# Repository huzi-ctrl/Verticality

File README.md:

# CanSat — Team Verticality (RP2040 Avionics & Dinoflagellate Bioluminescence Payload)

**Team Verticality** (Lancaster University School of Mathematics — UK CanSat Competition) is a 4-layer **52.0 mm round** avionics and dual-chamber biological payload controller built from scratch around the **Raspberry Pi RP2040** microcontroller.

Our secondary mission investigates **stress-induced mechano-bioluminescence** in marine dinoflagellates (***Pyrocystis fusiformis*** primary species; ***Pyrocystis lunula*** from Darwin Biological UK as the verified UK-stocked backup species) during rocket boost, parachute deployment, descent, and landing impact:
- **Chamber A (Warmed Experimental Culture)**: Actively maintained at **$22.0 \pm 1.0\text{ }^\circ\text{C}$** via a closed-loop PID controller driving an off-board $15\text{ }\Omega$, $2\text{ W}$ axial heating resistor (`R8`, switched by `Q1` `AO3400A` MOSFET at $1\text{ kHz}$ PWM) with a $10\text{ k}\Omega$ thin-film NTC thermistor (`TH1`). Safety cut-outs disable the heater if battery voltage drops below $3.50\text{ V}$ or Chamber A temperature reaches $30.0\text{ }^\circ\text{C}$.
- **Chamber B (Unheated Ambient Control)**: Identical optical geometry and cell concentration, left unheated with a matched $10\text{ k}\Omega$ NTC thermistor (`TH2`) to isolate temperature effects from mechanical shear and jerk ($\text{d}a/\text{d}t$).
- **Dual High-Sensitivity Optical Readout**: Two **AMS TSL2591** digital light sensor breakouts (`U7` on `I2C0`, `U8` on `I2C1` — separate hardware $\text{I}^2\text{C}$ buses because the `TSL2591` has a fixed `0x29` address) operating at $9876\times$ gain ($200\text{ ms}$ integration) inside light-tight black PETG chambers.
- **Pre-Touchdown Landing Leg Deployment & Upright Recovery**: Three 3D-printed curved landing legs folded against the **$64\text{ mm} \times 110\text{ mm}$** three-tier PETG cylindrical shell are released **during `DESCENT` before touchdown** — at **$150\text{ m}$ above pad altitude or $15\text{ s}$ after apogee, whichever comes first** — via an `MG90S` semi-metal servo (`J6`, low-side power-gated by `Q2` `AO3400A` so idle servo current is $0\text{ mA}$). The legs swing out to a **$140\text{ mm}$ triangular stance** while a $\sim 62\text{ g}$ steel ballast hatch lowers the centre of gravity to $z = 34\text{ mm}$ ($27\text{ mm}$ below the $61\text{ mm}$ leg pivot plane, giving a $>44^\circ$ static tip-over angle) so the top-mounted $433\text{ MHz}$ helical antenna stays upright after landing.

---

## 1. 3D PCB Renders & Layout Gallery

| Isometric 3D Render (`CanSat.kicad_pcb`) | Top View (`F.Cu` — RP2040, Flash, LDO, Ra-02, Power Stage) | Bottom View (`B.Cu` — Solid Ground Return & Signal Fanout) |
| :---: | :---: | :---: |
|  |  |  |

---

## 2. Mechanical Architecture, Landing Legs & Power Budget

### Three-Tier $64\text{ mm} \times 110\text{ mm}$ Shell & $52.0\text{ mm}$ Round PCB
The satellite body is a **$64\text{ mm}$ outer diameter $\times 110\text{ mm}$ tall** three-tier 3D-printed PETG structure clamped by **three $115\text{ mm}$ M3 A2 stainless steel threaded tie-rods** (`H1`, `H2`, `H3` on a $22.5\text{ mm}$ bolt-circle radius at $90^\circ, 210^\circ, 330^\circ$) to a top bulkhead lifting eyebolt:
1. **Top Tier ($40\text{ mm}$ height)**: Houses the **52.0 mm round 4-layer PCB**, the `Ai-Thinker Ra-02` ($433.175\text{ MHz}$ LoRa transceiver), U.FL pigtail, $21\text{ mm}$ helical antenna (`BW433SNX21-5W2`), `GY-BMP280-3.3` barometer (`U6`), and `Adafruit ADXL375` $\pm 200\text{ g}$ accelerometer (`U4`).
2. **Middle Tier ($42\text{ mm}$ height)**: Contains the light-tight black PETG **Chamber A** (heated to $22 \pm 1\text{ }^\circ\text{C}$ via `R8` $15\text{ }\Omega$ $2\text{ W}$ axial resistor and `TH1` NTC) and **Chamber B** (unheated control with `TH2` NTC), each with a sealed dinoflagellate vial and dedicated `TSL2591` optical sensor (`U7`, `U8`).
3. **Bottom Tier ($28\text{ mm}$ height)**: Houses the **flat `103450` $3.7\text{ V}$, $2000\text{ mAh}$ protected LiPo pouch cell** ($50 \times 34 \times 10\text{ mm}$ — selected specifically because a cylindrical 18650 cell is $65\text{ mm}$ long and cannot fit inside the $28\text{ mm}$ bottom tier or $64\text{ mm}$ diameter), the `MG90S` leg-release servo (`J6`), and the $\sim 62\text{ g}$ steel ballast hatch.

### Pre-Touchdown Leg Release Mechanism
- **Stowed Configuration**: Three curved 3D-printed PETG/TPU legs wrap flush against the outer wall during rocket integration and boost, held by a single nylon retention loop on the `MG90S` servo horn (`J6`).
- **In-Air Release (`STATE_DESCENT`)**: The flight software strictly locks out `Q2` (`GP9 = 0`) during `SELF_TEST`, `PAD`, and `BOOST`. Once apogee is passed (`STATE_DESCENT`) and either **relative altitude drops below $150.0\text{ m}$ above the pad OR $15.0\text{ s}$ have elapsed since apogee**, `GP9` turns on `Q2` (`AO3400A`) for $700\text{ ms}$ while `GP10` drives a $50\text{ Hz}$ PWM command to rotate the `MG90S` horn $120^\circ$, releasing all three legs before touchdown.
- **Self-Righting Geometry**: Torsion hinges open the three legs to a **$140\text{ mm}$ footprint** with hinges at $z = 61\text{ mm}$ above the base and the ballasted centre of gravity at $z = 34\text{ mm}$ ($27\text{ mm}$ below the pivot plane), providing a $>44^\circ$ static stability margin on uneven ground.

---

## 3. 4-Layer PCB Stackup, Layout Rules & Audit Compliance

The board ([`CanSat.kicad_pcb`](./CanSat.kicad_pcb)) is a **52.0 mm diameter**, $1.6\text{ mm}$ thick 4-layer FR-4 PCB designed to JLCPCB 4-layer manufacturing rules and verified against [`reports/CanSat_PCB_Design_Guide__Team_Verticality__rev2.pdf`](./reports/CanSat_PCB_Design_Guide__Team_Verticality__rev2.pdf):

| Layer | Copper Name | Plane / Function | Design Notes |
| :--- | :--- | :--- | :--- |
| **Layer 1** | `F.Cu` | Top Component & High-Speed Signal Layer | All **46 SMT components** placed on top side only (single-sided JLCPCB Economic PCBA); $90\text{ }\Omega$ differential USB (`R2`/`R3` = $22\text{ }\Omega$), short QSPI (`U2`), `12MHz` crystal (`Y1` + $33\text{ pF}$ C0G load caps `C10`/`C11`), and `0.6 mm` high-current switched paths (`Net-(Q1-D)` and `Net-(J6-Pin_1)`). |
| **Layer 2** | `In1.Cu` | Unbroken `GND` Reference Plane | Solid continuous ground reference plane beneath all high-speed, RF (`U5`), and analog (`ADC0..ADC2`) traces. |
| **Layer 3** | `In2.Cu` | `+3V3` Power Plane | Solid $+3.3\text{ V}$ distribution plane fed by `U3` (`MCP1700-3302E/TO`), with an explicit keepout cutout (`XTAL_KEEPOUT`) beneath `Y1`, `C10`, `C11`, and `R1` so crystal signals reference only `In1.Cu` (`GND`). |
| **Layer 4** | `B.Cu` | Bottom Signal Routing & `GND` Pour | Secondary signal fanout with stitched `GND` copper pour. Zero components on `B.Cu`. |

### Key Hardware & DFM Highlights
- **Strict SMT vs. Hand-Fit / Wire-Pad Separation**:
  - **46 SMT parts** (14 unique LCSC lines: 13 Basic + 1 Extended `RP2040` `C2040`, 157 SMT joints/board) have `LCSC` part numbers populated and are exported to [`production/parts_jlcpcb.csv`](./production/parts_jlcpcb.csv) and [`production/positions_jlcpcb.csv`](./production/positions_jlcpcb.csv).
  - **All 29 non-SMT items** — hand-fitted through-hole/castellated parts (`U3`, `U5`, `C22`, `J1`, `SW1`, `R8`), DNP $\text{I}^2\text{C}$ pull-up footprints (`R18–R21`), off-board module wire-pad groups (`U4`, `U6`, `U7`, `U8`, `TH1`, `TH2`, `J2`, `J3`, `J4`, `J5`, `J6`), test points (`TP1–TP5`), and mounting holes (`H1–H3`) — have **both `Exclude from bom` and `Exclude from Position Files`** set in [`CanSat.kicad_sch`](./CanSat.kicad_sch) and [`CanSat.kicad_pcb`](./CanSat.kicad_pcb).
- **High-Current MOSFET Via Arrays & Trace Widths**:
  - `Q1` (Heater `AO3400A`) and `Q2` (Servo `AO3400A`) each have **three `0.6 mm / 0.3 mm` `GND` vias** at their source pads (`Q1.2` and `Q2.2`) to handle the $\sim 1\text{ A}$ servo stall current and $250\text{ mA}$ heater current with minimal ground bounce.
  - `HighCurrent` netclass contains only the switched drain paths `Net-(Q1-D)` and `Net-(J6-Pin_1)` routed at **`0.6 mm` width**, while the logic gate nets (`/HEATER`, `/SERVO_P`, `/SERVO_S`) use signal widths.
- **Via Sizing & Standard JLCPCB $2.00 Base Tier Optimization**:
  - Every via on the board uses a **`0.30 mm` drill minimum** across all 112 vias (90 at `0.45 / 0.30 mm`, 3 at `0.50 / 0.30 mm`, and 19 at `0.60 / 0.30 mm` — zero `< 0.30 mm` vias remain), with `min_through_hole_diameter: 0.30` and `min_via_annular_width: 0.075` mm configured in [`CanSat.kicad_pro`](./CanSat.kicad_pro). This qualifies the design for JLCPCB's standard **`0.3mm / (0.4/0.45mm)`** pricing tier ($2.00 base price) instead of triggering advanced high-precision surcharges.
  - All 12 wire-pad groups (`J1/SW1`, `J2 BOOTSEL` using `CanSat_Modules:Pad_2pad_GND_SIG`, `J3 SWD`, `J4 USB`, `J5 RUN`, `J6 Servo`, `R8 Heater`, `TH1`, `TH2`, `U4`, `U6`, `U7`, `U8`) are protected by `WIRE_PADS` keepout zones prohibiting vias under solder pads, and teardrops are enabled on all pads and vias.
- **DRC & ERC Verification Status**:
  * [`DRC.rpt`](./DRC.rpt): **0 unconnected pads, 0 footprint errors, 0 schematic parity errors**.
  * **16 DFM Clearances Documented**:
    * **4 Hole-to-Hole Spacing Notices**: In the tight $0.4\text{ mm}$ pitch RP2040 escape fanout, adjacent $0.3\text{ mm}$ drill vias sit at $0.407\text{ mm}$ (`/INT_A` vs `/INT_B`) to $0.450\text{ mm}$ drill-edge spacing. While flagged against KiCad's generic $0.500\text{ mm}$ default rule, these safely clear JLCPCB's 4-layer CAM drill-to-drill capability of $\ge 0.25\text{ mm}$ (and $\ge 0.254\text{ mm}$ same-net).
    * **12 Drill-to-Track Clearances**: With $0.45\text{ mm}$ pads, $0.30\text{ mm}$ drills ($0.075\text{ mm}$ annular ring), and standard $0.15\text{ mm}$ trace clearance, physical drill-to-trace distance is $0.205\text{ mm} - 0.235\text{ mm}$, fully compliant with JLCPCB's 4-layer hole-to-track minimum of $\ge 0.20\text{ mm}$.
  * [`ERC.rpt`](./ERC.rpt): **0 ERC errors** (50 warnings for net-label wire stubs and unspecified pins per design guide).

---

## 4. Complete RP2040 Pin Allocation & Wire-Pad Pin Orders

### RP2040 (`U1`) GPIO & Peripheral Map

| RP2040 Pin | GPIO / Function | Schematic Net | Connected Component & Function |
| :---: | :--- | :--- | :--- |
| **Pin 2** | `GP0` (`UART0_TX`) | `/RX` | `TP4` UART Debug Header (MCU Transmit -> Adapter RX) |
| **Pin 3** | `GP1` (`UART0_RX`) | `/TX` | `TP5` UART Debug Header (MCU Receive <- Adapter TX) |
| **Pin 4** | `GP2` ( IRQ ) | `/INT_A` | `U7` (`TSL2591` Chamber A) Interrupt Output |
| **Pin 5** | `GP3` ( IRQ ) | `/INT_B` | `U8` (`TSL2591` Chamber B) Interrupt Output |
| **Pin 6** | `GP4` (`I2C0_SDA`) | `/SDA0` | `U7` (`TSL2591` Chamber A) $\text{I}^2\text{C}$ Data (`R18` DNP; pull-up on module) |
| **Pin 7** | `GP5` (`I2C0_SCL`) | `/SCL0` | `U7` (`TSL2591` Chamber A) $\text{I}^2\text{C}$ Clock (`R19` DNP; pull-up on module) |
| **Pin 8** | `GP6` (`I2C1_SDA`) | `/SDA1` | `U8` (`TSL2591` Chamber B) $\text{I}^2\text{C}$ Data (`R21` DNP; pull-up on module) |
| **Pin 9** | `GP7` (`I2C1_SCL`) | `/SCL1` | `U8` (`TSL2591` Chamber B) $\text{I}^2\text{C}$ Clock (`R20` DNP; pull-up on module) |
| **Pin 11** | `GP8` (`PWM4_A`) | `/HEATER` | `R7` ($100\text{ }\Omega$) & `R9` ($100\text{ k}\Omega$) $\rightarrow$ `Q1` (`AO3400A`) Gate $\rightarrow$ `R8` ($15\text{ }\Omega$ $2\text{ W}$ Chamber A Heater) |
| **Pin 12** | `GP9` (GPIO Out) | `/SERVO_P` | `R10` ($100\text{ }\Omega$) & `R11` ($100\text{ k}\Omega$) $\rightarrow$ `Q2` (`AO3400A`) Gate $\rightarrow$ `J6` (`MG90S` Low-Side Power Switch) |
| **Pin 13** | `GP10` (`PWM5_A`) | `/SERVO_S` | `R17` ($10\text{ k}\Omega$ pull-down) $\rightarrow$ `J6` Pin 3 (`MG90S` $50\text{ Hz}$ Servo PWM Signal) |
| **Pin 14** | `GP11` (`SPI1_CSn`) | `/PRESS_CS` | `U6` (`GY-BMP280-3.3`) SPI Chip Select |
| **Pin 15** | `GP12` (`SPI1_RX`) | `/IMU_MISO` | `U4` (`ADXL375`) & `U6` (`BMP280`) Shared `SPI1` MISO |
| **Pin 16** | `GP13` (`SPI1_CSn`) | `/IMU_CS` | `U4` (`ADXL375` $\pm 200\text{ g}$ Accelerometer) SPI Chip Select |
| **Pin 17** | `GP14` (`SPI1_SCK`) | `/IMU_SCLK` | `U4` (`ADXL375`) & `U6` (`BMP280`) Shared `SPI1` Clock |
| **Pin 18** | `GP15` (`SPI1_TX`) | `/IMU_MOSI` | `U4` (`ADXL375`) & `U6` (`BMP280`) Shared `SPI1` MOSI |
| **Pin 27** | `GP16` (`SPI0_RX`) | `/RA_MISO` | `U5` (`Ai-Thinker Ra-02` `SX1278` $433.175\text{ MHz}$ LoRa) MISO |
| **Pin 28** | `GP17` (`SPI0_CSn`) | `/RA_CS` | `U5` (`Ai-Thinker Ra-02`) NSS / Chip Select |
| **Pin 29** | `GP18` (`SPI0_SCK`) | `/RA_SCLK` | `U5` (`Ai-Thinker Ra-02`) SCK |
| **Pin 30** | `GP19` (`SPI0_TX`) | `/RA_MOSI` | `U5` (`Ai-Thinker Ra-02`) MOSI |
| **Pin 31** | `GP20` (GPIO Out) | `/RA_RESET` | `U5` (`Ai-Thinker Ra-02`) Hardware Reset |
| **Pin 32** | `GP21` (GPIO In) | `/RA_DIO0` | `U5` (`Ai-Thinker Ra-02`) `DIO0` TxDone / RxDone IRQ |
| **Pin 34** | `GP22` (GPIO In) | `/IMU_INT1` | `U4` (`ADXL375`) `INT1` High-G Shock Interrupt |
| **Pin 37** | `GP25` (GPIO Out) | `/LED` | `R12` ($1\text{ k}\Omega$) $\rightarrow$ `D1` (`KT-0805G` Green Status LED) |
| **Pin 38** | `GP26 / ADC0` | `/BATT_SENSE`| `R15` ($100\text{ k}\Omega$) / `R16` ($100\text{ k}\Omega$) $2:1$ Divider + `C25` ($100\text{ nF}$) from `/VBAT` |
| **Pin 39** | `GP27 / ADC1` | `/NTC_A` | `R13` ($10\text{ k}\Omega$ to `+3V3`) + `C23` ($100\text{ nF}$) + `TH1` (Chamber A $10\text{ k}\Omega$ NTC) |
| **Pin 40** | `GP28 / ADC2` | `/NTC_B` | `R14` ($10\text{ k}\Omega$ to `+3V3`) + `C24` ($100\text{ nF}$) + `TH2` (Chamber B $10\text{ k}\Omega$ NTC) |
| **Pin 46/47**| `USB_DM / USB_DP` | `/D-`, `/D+` | `R2` ($22\text{ }\Omega$) & `R3` ($22\text{ }\Omega$) $\rightarrow$ `J4` (`USB_3pad_wire`) |
| **Pin 51–56**| `QSPI_SD0..3, SCLK, SS` | `/SD0..3, /SCLK, /SS` | `U2` (`W25Q128JVSIQ` $16\text{ MB}$ QSPI Flash) + `R5` ($10\text{ k}\Omega$) + `R4` ($1\text{ k}\Omega$ to `J2` `BOOTSEL`) |

### Off-Board Wire-Pad Pin Orders (Design Guide Rev 2 Section 6)

| Footprint Ref | Module / Function | Pad Order on PCB |
| :---: | :--- | :--- |
| **`J1`** | Battery Input (`JST B2B-PH-K-S`) | `1 = /VBAT_R` (Battery $+$), `2 = GND` (Check LiPo red/black polarity before plugging in) |
| **`SW1`** | Master Slide Switch (`SS-12D00G3`) | `1 = open`, `2 = /VBAT_R` (middle common pin), `3 = /VBAT` (switched rail) |
| **`J2`** | `BOOTSEL` (`Pad_2pad_GND_SIG`) | `1 = GND`, `2 = Net-(J2-Pin_2)` (to `R4` $1\text{ k}\Omega \rightarrow \text{/SS}$) |
| **`J3`** | `SWD` (`SWD_3pad`) | `1 = /SWDIO`, `2 = GND`, `3 = /SWCLK` |
| **`J4`** | `USB` (`USB_3pad_wire`) | `1 = GND`, `2 = /D-`, `3 = /D+` (Board powered from battery during USB flashing) |
| **`J5`** | `RUN` (`Pad_2pad_GND_SIG`) | `1 = GND`, `2 = /RUN` |
| **`J6`** | `MG90S` Servo (`Pad_3pad_Servo`) | `1 = Net-(J6-Pin_1)` (switched GND via `Q2` — brown), `2 = /VBAT` (red), `3 = /SERVO_S` (orange) |
| **`R8`** | Chamber A Heater ($15\text{ }\Omega$ $2\text{ W}$) | `1 = Net-(Q1-D)` (switched GND via `Q1`), `2 = /VBAT` |
| **`TH1` / `TH2`** | Chamber A / B NTC ($10\text{ k}\Omega$) | `1 = /NTC_A` (or `/NTC_B`), `2 = GND` |
| **`U4`** | `ADXL375` Breakout (`Pad_7pad_ADXL375`) | `1/6 = +3V3`, `2/4/5 = GND`, `7 = /IMU_CS`, `8 = /IMU_INT1`, `12 = /IMU_MISO`, `13 = /IMU_MOSI`, `14 = /IMU_SCLK` |
| **`U6`** | `GY-BMP280-3.3` (`Pad_6pad_BMP280`) | `1/7 = GND`, `2 = /PRESS_CS`, `3 = /IMU_MOSI`, `4 = /IMU_SCLK`, `5 = /IMU_MISO`, `6/8 = +3V3` |
| **`U7` / `U8`** | `TSL2591` Breakout A / B (`TSL2591_module_5pad`) | `1 = +3V3`, `2 = GND`, `3 = /SDA0` (`/SDA1`), `4 = /SCL0` (`/SCL1`), `5 = /INT_A` (`/INT_B`) |

---

## 5. Firmware Architecture & 34-Byte Binary Telemetry Frame

All MicroPython flight and ground-station software resides in [`firmware/`](./firmware/):
- **[`firmware/main.py`](./firmware/main.py)**: Implements the 5-state flight state machine (`0: SELF_TEST`, `1: PAD`, `2: BOOST`, `3: DESCENT`, `4: LANDED`), the 5-second pre-launch RAM ring buffer, the $22.0 \pm 1.0\text{ }^\circ\text{C}$ Chamber A PID controller (with $<3.50\text{ V}$ and $\ge 30.0\text{ }^\circ\text{C}$ safety cut-outs), pre-touchdown leg release in `DESCENT` at $<150\text{ m}$ above pad or $\ge 15\text{ s}$ post-apogee, full-rate flash CSV logging (`flight_log.csv`), and $1\text{ Hz}$ binary LoRa transmission at $433.175\text{ MHz}$ (`SF8, BW125, CR4/5`).
- **[`firmware/sensors.py`](./firmware/sensors.py)**: Hardware drivers for `BMP280` (`SPI1`), `ADXL375` $\pm 200\text{ g}$ (`SPI1`), dual `TSL2591` (`I2C0` & `I2C1`), Steinhart-Hart $10\text{ k}\Omega$ NTC thermistors (`ADC1`, `ADC2`), and battery voltage divider (`ADC0`).
- **[`firmware/sx1278.py`](./firmware/sx1278.py)**: `SPI0` register-level driver for the `Ai-Thinker Ra-02` (`Semtech SX1278`) configured for $433.175\text{ MHz}$, `SF8`, `BW 125 kHz`, `CR 4/5`, `+17 dBm`.
- **[`firmware/ground_station.py`](./firmware/ground_station.py)**: Ground receiver that unpacks the 34-byte binary frame, verifies its 16-bit `CRC-CCITT` checksum (skipping corrupted frames without crashing per Test `T7`), writes two redundant CSV logs (`ground_log_primary.csv` and `ground_log_backup.csv`), and streams live telemetry over USB serial.

### 34-Byte Little-Endian Binary Telemetry Packet Specification (PDR Appendix D)

Packed with `struct.pack("<HBIIhhhIIHHHBH", ...)` ($34\text{ bytes}$ total, $\sim 120\text{ ms}$ airtime at `SF8 / BW125 / CR4/5`):

| Byte Offset | Field Name | C / Python Type | Size | Units / Scaling & Description |
| :---: | :--- | :---: | :---: | :--- |
| `0..1` | `pkt_num` | `uint16` (`H`) | 2 B | Monotonic packet sequence counter (`0..65535`) |
| `2` | `state` | `uint8` (`B`) | 1 B | Flight state: `0=SELF_TEST, 1=PAD, 2=BOOST, 3=DESCENT, 4=LANDED` |
| `3..6` | `mission_time_ms` | `uint32` (`I`) | 4 B | Milliseconds elapsed since boot |
| `7..10` | `pressure_pa` | `uint32` (`I`) | 4 B | Barometric pressure from `BMP280` in $\text{Pa}$ |
| `11..12` | `air_temp_c_x100` | `int16` (`h`) | 2 B | External air temperature from `BMP280` in $0.01\text{ }^\circ\text{C}$ |
| `13..14` | `chamber_a_temp_x100` | `int16` (`h`) | 2 B | Heated Chamber A temperature (`TH1`) in $0.01\text{ }^\circ\text{C}$ |
| `15..16` | `chamber_b_temp_x100` | `int16` (`h`) | 2 B | Unheated Control Chamber B temperature (`TH2`) in $0.01\text{ }^\circ\text{C}$ |
| `17..20` | `light_a` | `uint32` (`I`) | 4 B | Chamber A `TSL2591` (`U7`) visible bioluminescence counts |
| `21..24` | `light_b` | `uint32` (`I`) | 4 B | Chamber B `TSL2591` (`U8`) visible bioluminescence counts |
| `25..26` | `peak_accel_g_x10` | `uint16` (`H`) | 2 B | Peak acceleration magnitude $|a|$ over $1\text{ s}$ window in $0.1\text{ g}$ |
| `27..28` | `rms_jerk_gps` | `uint16` (`H`) | 2 B | RMS mechanical jerk $|\text{d}a/\text{d}t|$ over $1\text{ s}$ window in $\text{g/s}$ |
| `29..30` | `battery_mv` | `uint16` (`H`) | 2 B | LiPo battery voltage (`VBAT`) in $\text{mV}$ |
| `31` | `heater_duty_pct` | `uint8` (`B`) | 1 B | Chamber A PWM heater duty cycle (`0–100 %`) |
| `32..33` | `crc16` | `uint16` (`H`) | 2 B | `CRC-16-CCITT` (`poly=0x1021, init=0xFFFF`) over bytes `0..31` |

---

## 6. Verification & Test Plan Summary (T1–T10, PDR Section 5)

| Test ID | Verification Test | Method & Acceptance Target | Status / Design Verification |
| :---: | :--- | :--- | :--- |
| **T1** | **Mass, Dimensions & Fit Check** | Measure OD/height in launch tube simulator and weigh on $0.1\text{ g}$ balance. Target: $\text{OD} \le 64.5\text{ mm}$, $H \le 110\text{ mm}$, mass $300\text{–}330\text{ g}$ ($312\text{ g}$ nominal with $62\text{ g}$ ballast). | $52.0\text{ mm}$ round PCB fits inside $64\text{ mm}$ shell with $2.5\text{ mm}$ M3 tie-rod clearance (`MECH_KEEPOUT`). |
| **T2** | **Parachute Deployment Shock Load** | Hang $5.2\text{ kg}$ static load ($>150\text{ N}$ shock equivalent) from top eyebolt and swivel (`35–43 kg` barrel swivel) for $60\text{ s}$. Target: zero structural cracking or thread pull-out. | Load path goes directly through the 3 stainless M3 tie-rods, bypassing the PETG shell walls and PCB. |
| **T3** | **Descent Rate & Balcony Drop** | Drop weighted $312\text{ g}$ prototype with $38\text{ cm}$ octo-annular ripstop canopy from $10\text{ m}$. Target: steady descent $8.0\text{–}9.2\text{ m/s}$ ($8.6\text{ m/s}$ nominal). | Sized in PDR Section 3; verified by `BMP280` $\text{d}h/\text{d}t$ logging. |
| **T4** | **Cold-Soak Battery & Heater Endurance** | Run complete avionics + Chamber A heater + $1\text{ Hz}$ LoRa inside $4\text{ }^\circ\text{C}$ fridge for $2.5\text{ hours}$. Target: Chamber A holds $22.0 \pm 1.0\text{ }^\circ\text{C}$ for $\ge 90\text{ min}$; `VBAT` stays $>3.50\text{ V}$. | `103450` $2000\text{ mAh}$ pouch cell provides $>2.4\times$ margin over the $820\text{ mAh}$ mission budget. |
| **T5** | **Dark-Chamber Light-Tightness** | Place `TSL2591` inside sealed Chambers A & B under $50{,}000\text{ lux}$ floodlight (`GAIN_MAX = 9876x`). Target: baseline reading $< 5\text{ counts}$ with zero light leakage. | Labyrinth O-ring cap and black PETG walls block external light. |
| **T6** | **Vortex-Shaker Bioluminescence Curve** | Stimulate dark-adapted *Pyrocystis* vials during the nocturnal phase of their $12:12$ cycle at graded RPMs while logging `ADXL375` jerk and `TSL2591` counts. | Confirms positive correlation between RMS jerk ($\text{g/s}$) and flash intensity, and higher output at $22\text{ }^\circ\text{C}$ vs. cold control. |
| **T7** | **LoRa Range & Corrupted-Packet Fuzzing** | Line-of-sight range walk to $\ge 1.2\text{ km}$ at $433.175\text{ MHz}$ (`SF8`), plus injection of truncated/bit-flipped frames into `ground_station.py`. Target: $>95\%$ packet reception; zero parser crashes. | `decode_telemetry_frame()` validates length ($34\text{ B}$) and `CRC-16-CCITT` before logging. |
| **T8** | **Two-Point Sensor Calibration** | Calibrate `TH1`, `TH2`, and `BMP280` against a reference thermometer ($0\text{ }^\circ\text{C}$ ice bath to $35\text{ }^\circ\text{C}$ water bath) and check `ADXL375` $\pm 1\text{ g}$ six-face inversions. | Steinhart-Hart coefficients and baseline pressure `alt_0` stored in [`firmware/sensors.py`](./firmware/sensors.py). |
| **T9** | **Brownout & Reboot State Recovery** | Interrupt battery power for $50\text{ ms}$ and $2\text{ s}$ during simulated `DESCENT`. Target: `RP2040` reboots cleanly, appends to `flight_log.csv` without overwriting prior data. | `open("flight_log.csv", "a")` with periodic `flush()` every 5 packets. |
| **T10** | **End-to-End Vacuum-Jar Flight Simulation** | Place CanSat in sealed vacuum chamber, pump down to simulate ascent $>25\text{ m}$ (`BOOST`), vent past apogee (`DESCENT`), and verify pre-touchdown leg release. | Servo fires in `DESCENT` at $<150\text{ m}$ or $15\text{ s}$ post-apogee; locked out in `SELF_TEST`, `PAD`, and `BOOST`. |

---

## 7. Complete Verified Bill of Materials (`$199.53` USD / `£154.10` Total inc. VAT & Delivery)

The authoritative project bom is tracked in [`bom.csv`](./BOM.csv) (formatted for Hack Club Half-Life in USD), [`CanSat_schematic_to_parts_map.csv`](./CanSat_schematic_to_parts_map.csv), and [`CanSat_parts_verified_direct_links.xlsx`](./CanSat_parts_verified_direct_links.xlsx), split across 5 orders:
- **Order 1 — JLCPCB PCB + Top-Side SMT Assembly ([`production/parts_jlcpcb.csv`](./production/parts_jlcpcb.csv))**: 14 unique SMT lines (**46 placed parts**, **157 SMT joints/board**, 2 assembled boards, 5 bare 4-layer boards) = **$15.28 USD** / **£40.41** (inc. 20% VAT & shipping).
- **Order 2 — LCSC Hand-Fit Basket**: `U5` (`Ra-02`), `U3` (`MCP1700-3302E/TO`), `C22` ($100\text{ }\mu\text{F}$), `J1` (`JST-PH`), `SW1` (`SS-12D00G3`), `R8` ($15\text{ }\Omega$ $2\text{ W}$ axial heater), and $433\text{ MHz}$ helical antenna = **$11.22 USD** / **£22.09** (inc. 20% VAT & shipping).
- **Order 3 — UK / Overseas Modules & Mechanical Hardware**: `U4` (`Adafruit ADXL375`), `U6` (`GY-BMP280-3.3`), `U7`/`U8` (`2x TSL2591`), `TH1`/`TH2` (`2x 10k NTC`), `103450` $2000\text{ mAh}$ LiPo pouch cell, `TP4056` charger, `MG90S` servo, ripstop nylon, barrel swivels, M3 stainless tie-rods, lifting eyebolt, and U.FL pigtail = **$70.83 USD** / **£52.59** (inc. VAT & delivery).
- **Order 4 — Biology (Darwin Biological UK)**: *Pyrocystis* starter culture, Marine Algae Growth Medium vial, tracked courier delivery, and VAT = **$37.64 USD** / **£39.00** (inc. 20% VAT; £32.50 ex VAT if reclaimed via school finance).
- **Order 5 — School Lab & Workshop Stock**: Sterile seawater base, $12:12$ light timer, vials, PETG/TPU 3D-printing filament (including the 3D-printed legs), scrap steel ballast, M3 Nyloc nuts, USB lead, and 550 paracord = **$0.00**.

> [!NOTE]
> **Hack Club Half-Life Grant Submission Summary ([`bom.csv`](./BOM.csv))**:
> - **Total Parts Cost**: **$134.97 USD** (42 build items, parts only, zero tools)
> - **Tax & Shipping for the Whole Order**: **$64.56 USD**
> - **Grand Total**: **$199.53 USD** (fully compliant with the $200 Hack Club hardware grant cap)

### Order 1: JLCPCB Factory-Assembled SMT Parts ([`production/parts_jlcpcb.csv`](./production/parts_jlcpcb.csv))

| Designators | Qty/Board | Value / Spec | Package | LCSC Code | PCBA Type |
| :--- | :---: | :--- | :--- | :---: | :---: |
| `U1` | 1 | `RP2040` Dual Cortex-M0+ MCU | `QFN-56-1EP_7x7mm_P0.4mm_EP3.2x3.2mm` | `C2040` | Extended |
| `U2` | 1 | `W25Q128JVSIQ` $16\text{ MB}$ QSPI Flash | `SOIC-8_5.3x5.3mm_P1.27mm` | `C97521` | Basic |
| `Y1` | 1 | `12MHz` $20\text{ pF}$ SMD Crystal (`X322512MSB4SI`) | `Crystal_SMD_3225-4Pin_3.2x2.5mm` | `C9002` | Basic |
| `C10, C11` | 2 | `33pF` $50\text{ V}$ `C0G` Crystal Load Caps | `C_0402_1005Metric` | `C1562` | Basic |
| `C1–C9, C14, C15, C18–C21, C23–C25` | 18 | `100nF` $16\text{ V}$ `X7R` Decoupling & Filter Caps | `C_0402_1005Metric` | `C1525` | Basic |
| `C13, C16` | 2 | `1uF` $25\text{ V}$ `X5R` RP2040 Core/VREG Caps | `C_0402_1005Metric` | `C52923` | Basic |
| `C12, C17` | 2 | `10uF` $10\text{ V}$ `X5R` LDO Bulk Caps | `C_0603_1608Metric` | `C19702` | Basic |
| `Q1, Q2` | 2 | `AO3400A` $30\text{ V}$ $5.7\text{ A}$ N-MOSFET | `SOT-23` | `C20917` | Basic |
| `D1` | 1 | Green Status LED (`KT-0805G`) | `LED_0805_2012Metric` | `C2297` | Basic |
| `R1, R4, R12` | 3 | `1k` $\pm 1\%$ Resistor (Crystal, BOOTSEL, LED) | `R_0402_1005Metric` | `C11702` | Basic |
| `R2, R3` | 2 | `22` $\Omega$ $\pm 1\%$ USB Series Termination | `R_0402_1005Metric` | `C25092` | Basic |
| `R5, R6, R13, R14, R17` | 5 | `10k` $\pm 1\%$ Resistor (SS, RUN, NTCs, Servo Pull-Down) | `R_0402_1005Metric` | `C25744` | Basic |
| `R7, R10` | 2 | `100` $\Omega$ $\pm 1\%$ MOSFET Gate Series | `R_0402_1005Metric` | `C25076` | Basic |
| `R9, R11, R15, R16` | 4 | `100k` $\pm 1\%$ Gate Pull-Downs & `VBAT` Divider | `R_0402_1005Metric` | `C25741` | Basic |
| *`R18, R19, R20, R21`* | *0 (DNP)* | *`4.7k` DNP (`Exclude from bom & Pos` — pull-ups on `TSL2591` modules)* | *`R_0402_1005Metric`* | *`C25900`* | *DNP* |

---

## 8. Repository Structure

```text
CanSat/
├── CanSat.kicad_pro                # KiCad 10 Project (strict DRC severities, min_via=0.45mm, HighCurrent netclass)
├── CanSat.kicad_sch                # Complete Schematic (exclude flags & LCSC codes synchronized with PCB)
├── CanSat.kicad_pcb                # 4-Layer 52.0 mm Round PCB Layout (0 unconnected items, 0.3mm via drills)
├── CanSat.kicad_dru                # Custom Design Rules (Rev 2: fanout, via>=0.45mm, HighCurrent>=0.6mm, USB skew)
├── CanSat_Modules.pretty/          # Custom Footprint Library (Pad_2pad_GND_SIG, Pad_3pad_Servo, ADXL375, BMP280, TSL2591)
├── DRC.rpt                         # Official KiCad DRC & Parity Report (0 unconnected, 0 parity errors, 16 DFM notices)
├── ERC.rpt                         # Official KiCad ERC Report (0 errors)
├── schematic.pdf                   # Exported Vector Schematic PDF
├── BOM.csv                         # Complete Verified Project bom for Hack Club ($199.53 USD total / £154.10 inc. tax & shipping)
├── TEACHER_REQUISITION.md          # Clean School Teacher Requisition (Darwin Biological & £20-30 Order)
├── CanSat_schematic_to_parts_map.csv # Authoritative Designator-to-parts & Placement Map (72 schematic parts)
├── CanSat_parts_verified_direct_links.xlsx # Verified Pricing & Direct Supplier Links Spreadsheet
├── production/                     # Ready-to-Order JLCPCB Manufacturing Package
│   ├── gerbers.zip                 # 4-Layer Gerber + Excellon Drill Archive (regenerated from final PCB)
│   ├── parts_jlcpcb.csv            # JLCPCB SMT Assembly Parts (14 lines / 46 SMT parts / 157 joints only)
│   └── positions_jlcpcb.csv        # JLCPCB SMT Pick-and-Place File (46 top-side SMT parts only)
├── firmware/                       # RP2040 MicroPython Flight & Ground Station Software
│   ├── main.py                     # 5-State Flight Loop, 22°C Heater PID, Pre-Touchdown Leg Release, 34B Binary Telemetry
│   ├── sensors.py                  # Drivers for BMP280 (SPI1), ADXL375 (SPI1), Dual TSL2591 (I2C0/1), NTCs & VBAT
│   ├── sx1278.py                   # Ai-Thinker Ra-02 (SX1278 433.175 MHz, SF8, BW125, CR4/5) LoRa Driver
│   └── ground_station.py           # 34-Byte Binary + CRC16 Receiver & Redundant Dual-CSV Telemetry Logger
├── reports/                        # Preliminary Design Review (PDR) & PCB Design Guide
│   ├── LUSoM_Team_Verticality_PDR_updated_v2.pdf
│   └── CanSat_PCB_Design_Guide__Team_Verticality__rev2.pdf
├── images/                         # Raytraced 3D PCB Renders & Schematic Previews
└── LICENSE                         # MIT License
```

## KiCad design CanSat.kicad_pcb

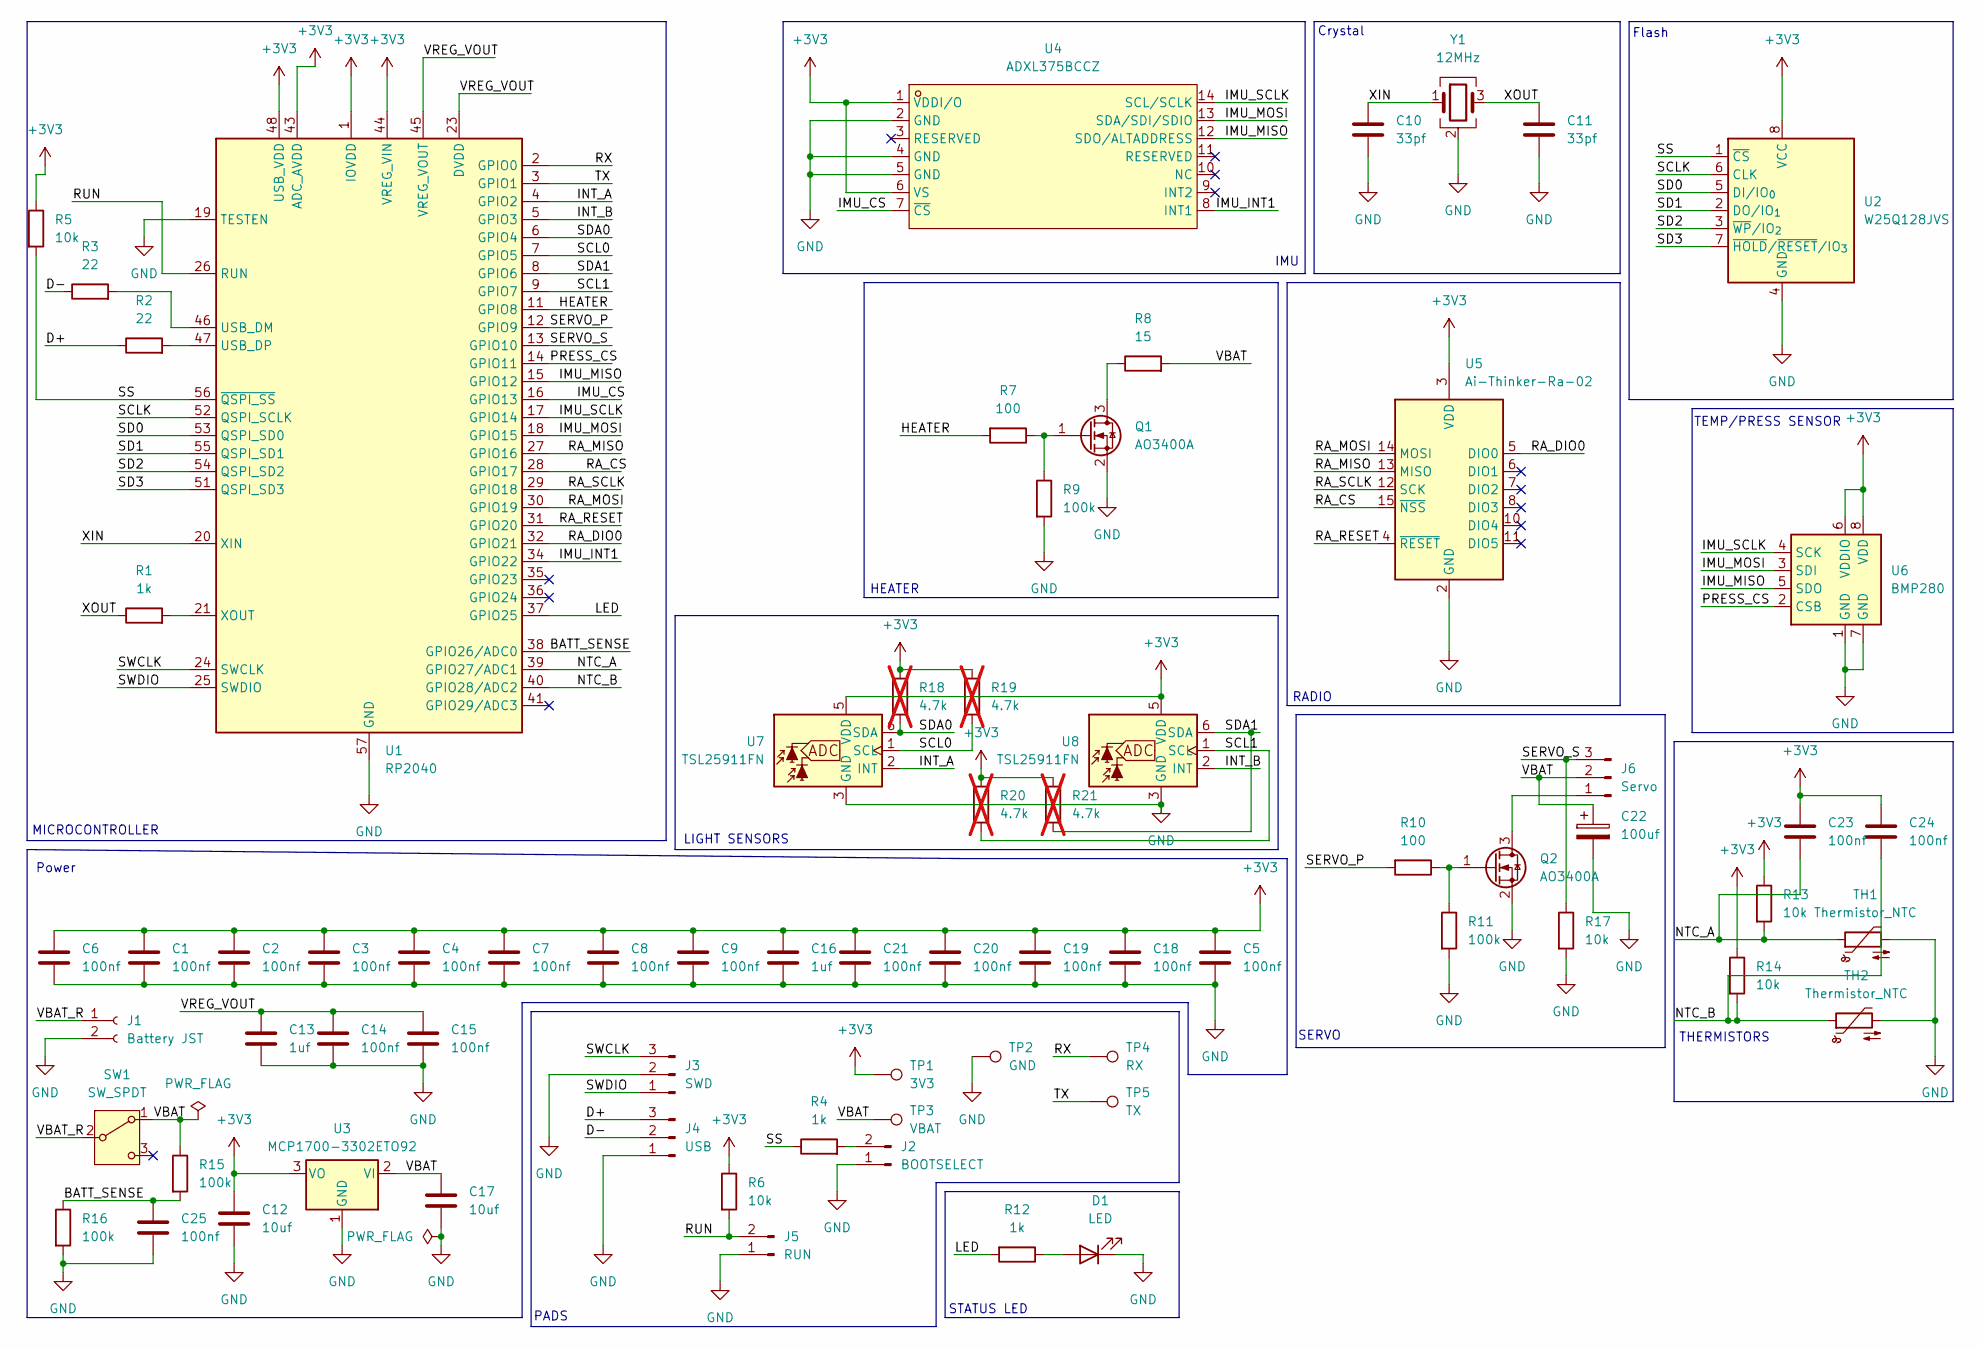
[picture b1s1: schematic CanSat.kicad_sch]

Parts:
C1, C2, C3, C4, C5, C6, C7, C8, C9, C14, C15, C18, C19, C20, C21, C23, C24, C25: 100nf; C_0402_1005Metric
C10, C11: 33pf; C_0402_1005Metric
C12, C17: 10uf; C_0603_1608Metric
C13, C16: 1uf; C_0402_1005Metric
C22: 100uf; CP_Radial_D5.0mm_P2.00mm
D1: LED; LED_0805_2012Metric
J1: Battery JST; JST_PH_B2B-PH-K_1x02_P2.00mm_Vertical
J2: BOOTSELECT; Pad_2pad_GND_SIG
J3: SWD; SWD_3pad
J4: USB; USB_3pad_wire
J5: RUN; Pad_2pad_GND_SIG
J6: Servo; Servo_3pad
Q1, Q2: AO3400A; SOT-23
R1, R4, R12: 1k; R_0402_1005Metric
R2, R3: 22; R_0402_1005Metric
R5, R6, R13, R14, R17: 10k; R_0402_1005Metric
R7, R10: 100; R_0402_1005Metric
R8: 15; Heater_2pad
R9, R11, R15, R16: 100k; R_0402_1005Metric
R18, R19, R20, R21: 4.7k; R_0402_1005Metric; not fitted
SW1: SW_SPDT; SW_SlideSwitch_3pad_wire
TH1, TH2: Thermistor_NTC; NTC_2pad
TP1: 3V3; TestPoint_Pad_D1.5mm
TP2: GND; TestPoint_Pad_D1.5mm
TP3: VBAT; TestPoint_Pad_D1.5mm
TP4: RX; TestPoint_Pad_D1.5mm
TP5: TX; TestPoint_Pad_D1.5mm
U1: RP2040; QFN-56-1EP_7x7mm_P0.4mm_EP3.2x3.2mm
U2: W25Q128JVS; SOIC-8_5.3x5.3mm_P1.27mm
U3: MCP1700-3302ETO92; TO-92_Inline
U4: ADXL375BCCZ; ADXL375_module_chippins; MPN ADXL375BCCZ; LCSC Part C579466
U5: Ai-Thinker-Ra-02; Ai-Thinker-Ra-01-LoRa
U6: BMP280; BMP280_module_chippins
U7, U8: TSL25911FN; TSL2591_module_chippins
Y1: 12MHz; Crystal_SMD_3225-4Pin_3.2x2.5mm

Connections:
+3V3: C1.1, C2.1, C3.1, C4.1, C5.1, C6.1, C7.1, C8.1, C9.1, C12.1, C16.1, C18.1, C19.1, C20.1, C21.1, C23.1, C24.1, R5.1, R6.1, R13.1, R14.1, R18.1, R19.1, R20.1, R21.1, TP1.1 (1_1), U1.1 (IOVDD), U1.10 (IOVDD), U1.22 (IOVDD), U1.33 (IOVDD), U1.42 (IOVDD), U1.43 (ADC_AVDD), U1.44 (VREG_VIN), U1.48 (USB_VDD), U1.49 (IOVDD), U2.8 (VCC), U3.3 (VO), U4.1 (VDDI/O), U4.6 (VS), U5.3 (VDD), U6.6 (VDDIO), U6.8 (VDD), U7.5 (VDD), U8.5 (VDD)
/BATT_SENSE: C25.1, R15.2, R16.1, U1.38 (GPIO26/ADC0)
/D+: J4.3, R2.1
/D-: J4.2, R3.1
/HEATER: R7.2, U1.11 (GPIO8)
/IMU_CS: U1.16 (GPIO13), U4.7 (~CS)
/IMU_INT1: U1.34 (GPIO22), U4.8 (INT1)
/IMU_MISO: U1.15 (GPIO12), U4.12 (SDO/ALTADDRESS), U6.5 (SDO)
/IMU_MOSI: U1.18 (GPIO15), U4.13 (SDA/SDI/SDIO), U6.3 (SDI)
/IMU_SCLK: U1.17 (GPIO14), U4.14 (SCL/SCLK), U6.4 (SCK)
/INT_A: U1.4 (GPIO2), U7.2 (INT)
/INT_B: U1.5 (GPIO3), U8.2 (INT)
/LED: R12.2, U1.37 (GPIO25)
/NTC_A: C23.2, R13.2, TH1.1, U1.39 (GPIO27/ADC1)
/NTC_B: C24.2, R14.2, TH2.1, U1.40 (GPIO28/ADC2)
/PRESS_CS: U1.14 (GPIO11), U6.2 (CSB)
/RA_CS: U1.28 (GPIO17), U5.15 (~NSS)
/RA_DIO0: U1.32 (GPIO21), U5.5 (DIO0)
/RA_MISO: U1.27 (GPIO16), U5.13 (MISO)
/RA_MOSI: U1.30 (GPIO19), U5.14 (MOSI)
/RA_RESET: U1.31 (GPIO20), U5.4 (~RESET)
/RA_SCLK: U1.29 (GPIO18), U5.12 (SCK)
/RUN: J5.2, R6.2, U1.26 (RUN)
/RX: TP4.1 (1_1), U1.2 (GPIO0)
/SCL0: R19.2, U1.7 (GPIO5), U7.1 (SCL)
/SCL1: R20.2, U1.9 (GPIO7), U8.1 (SCL)
/SCLK: U1.52 (QSPI_SCLK), U2.6 (CLK)
/SD0: U1.53 (QSPI_SD0), U2.5 (DI/IO_{0})
/SD1: U1.55 (QSPI_SD1), U2.2 (DO/IO_{1})
/SD2: U1.54 (QSPI_SD2), U2.3 (~WP/IO_{2})
/SD3: U1.51 (QSPI_SD3), U2.7 (~HOLD/~RESET/IO_{3})
/SDA0: R18.2, U1.6 (GPIO4), U7.6 (SDA)
/SDA1: R21.2, U1.8 (GPIO6), U8.6 (SDA)
/SERVO_P: R10.2, U1.12 (GPIO9)
/SERVO_S: J6.3, R17.1, U1.13 (GPIO10)
/SS: R4.1, R5.2, U1.56 (~QSPI_SS), U2.1 (~CS)
/SWCLK: J3.3, U1.24 (SWCLK)
/SWDIO: J3.1, U1.25 (SWDIO)
/TX: TP5.1 (1_1), U1.3 (GPIO1)
/VBAT: C17.1, C22.1, J6.2, R8.2, R15.1, SW1.1 (A), TP3.1 (1_1), U3.2 (VI)
/VBAT_R: J1.1, SW1.2 (B)
/VREG_VOUT: C13.1, C14.1, C15.1, U1.23 (DVDD), U1.45 (VREG_VOUT), U1.50 (DVDD)
/XIN: C10.1, U1.20 (XIN), Y1.1
/XOUT: C11.1, R1.1, Y1.3
GND: C1.2, C2.2, C3.2, C4.2, C5.2, C6.2, C7.2, C8.2, C9.2, C10.2, C11.2, C12.2, C13.2, C14.2, C15.2, C16.2, C17.2, C18.2, C19.2, C20.2, C21.2, C22.2, C25.2, D1.1 (K), J1.2, J2.1, J3.2, J4.1, J5.1, Q1.2 (S), Q2.2 (S), R9.2, R11.2, R16.2, R17.2, TH1.2, TH2.2, TP2.1 (1_1), U1.19 (TESTEN), U1.57 (GND), U2.4 (GND), U3.1 (GND), U4.2 (GND), U4.4 (GND), U4.5 (GND), U5.1 (GND), U5.2 (GND), U5.9 (GND), U5.16 (GND), U6.1 (GND), U6.7 (GND), U7.3 (GND), U8.3 (GND), Y1.2 (G), Y1.4 (G)
unnamed: D1.2 (A), R12.1
unnamed: J2.2, R4.2
unnamed: J6.1, Q2.3 (D)
unnamed: Q1.3 (D), R8.1
unnamed: Q1.1 (G), R7.1, R9.1
unnamed: Q2.1 (G), R10.1, R11.1
unnamed: R3.2, U1.46 (USB_DM)
unnamed: R2.2, U1.47 (USB_DP)
unnamed: R1.2, U1.21 (XOUT)

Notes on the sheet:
Power
Flash
HEATER
LIGHT SENSORS
MICROCONTROLLER
STATUS LED
PADS
Crystal
IMU
TEMP/PRESS SENSOR
THERMISTORS
SERVO
RADIO

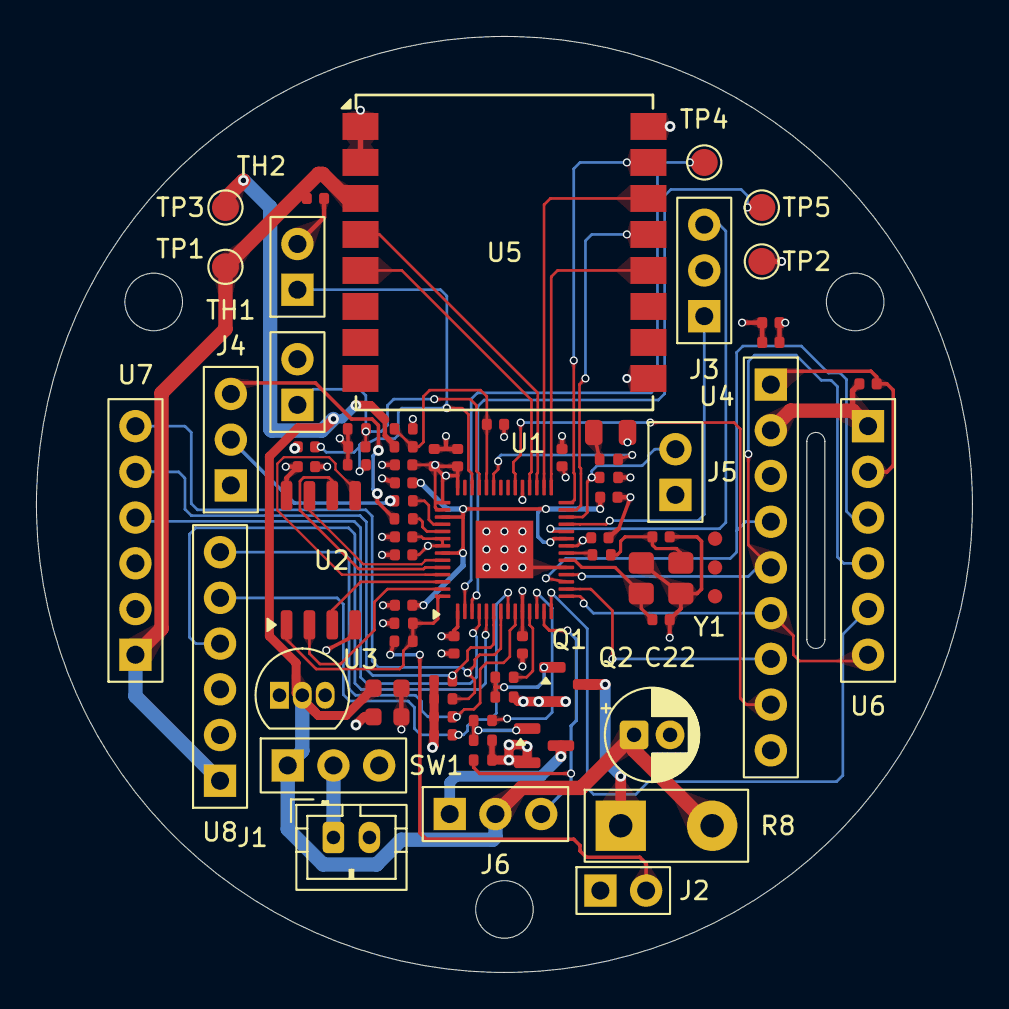
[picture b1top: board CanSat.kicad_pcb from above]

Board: 4 copper layers, 52.0 x 52.0 mm, 75 parts (0 on the bottom side), 54 nets.

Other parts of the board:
H1, H2, H3: M3_TieRod; MountingHole_3.2mm_M3

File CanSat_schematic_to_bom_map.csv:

Designator,Value (bom),Suggested footprint,LCSC / source,Who fits it,Note,Current schematic footprint
C1,100nF,Capacitor_SMD:C_0402_1005Metric,C1525,JLCPCB,,NONE
C2,100nF,Capacitor_SMD:C_0402_1005Metric,C1525,JLCPCB,,NONE
C3,100nF,Capacitor_SMD:C_0402_1005Metric,C1525,JLCPCB,,NONE
C4,100nF,Capacitor_SMD:C_0402_1005Metric,C1525,JLCPCB,,NONE
C5,100nF,Capacitor_SMD:C_0402_1005Metric,C1525,JLCPCB,,NONE
C6,100nF,Capacitor_SMD:C_0402_1005Metric,C1525,JLCPCB,,NONE
C7,100nF,Capacitor_SMD:C_0402_1005Metric,C1525,JLCPCB,,NONE
C8,100nF,Capacitor_SMD:C_0402_1005Metric,C1525,JLCPCB,,NONE
C9,100nF,Capacitor_SMD:C_0402_1005Metric,C1525,JLCPCB,,NONE
C10,33pF C0G,Capacitor_SMD:C_0402_1005Metric,C1562,JLCPCB,,NONE
C11,33pF C0G,Capacitor_SMD:C_0402_1005Metric,C1562,JLCPCB,,NONE
C12,10uF 10V,Capacitor_SMD:C_0603_1608Metric,C19702,JLCPCB,,NONE
C13,1uF,Capacitor_SMD:C_0402_1005Metric,C52923,JLCPCB,,NONE
C14,100nF,Capacitor_SMD:C_0402_1005Metric,C1525,JLCPCB,,NONE
C15,100nF,Capacitor_SMD:C_0402_1005Metric,C1525,JLCPCB,,NONE
C16,1uF,Capacitor_SMD:C_0402_1005Metric,C52923,JLCPCB,,NONE
C17,10uF 10V,Capacitor_SMD:C_0603_1608Metric,C19702,JLCPCB,,NONE
C18,100nF,Capacitor_SMD:C_0402_1005Metric,C1525,JLCPCB,,NONE
C19,100nF,Capacitor_SMD:C_0402_1005Metric,C1525,JLCPCB,,NONE
C20,100nF,Capacitor_SMD:C_0402_1005Metric,C1525,JLCPCB,,NONE
C21,100nF,Capacitor_SMD:C_0402_1005Metric,C1525,JLCPCB,,NONE
C22,100uF 16V,Capacitor_THT:CP_Radial_D5.0mm_P2.00mm,C43803,Hand-fit (LCSC),Exclude from bom and position files.,NONE
C23,100nF,Capacitor_SMD:C_0402_1005Metric,C1525,JLCPCB,,NONE
C24,100nF,Capacitor_SMD:C_0402_1005Metric,C1525,JLCPCB,,NONE
C25,100nF,Capacitor_SMD:C_0402_1005Metric,C1525,JLCPCB,,NONE
D1,LED green,LED_SMD:LED_0805_2012Metric,C2297,JLCPCB,,NONE
J1,JST B2B-PH-K-S,Connector_JST:JST_PH_B2B-PH-K_1x02_P2.00mm_Vertical,C131337,Hand-fit (LCSC),Check pin 1 = battery + against the LiPo plug.,NONE
J2,BOOTSEL,Pad_2pad_GND_SIG (custom),-,Pad only,"Pin1 GND, pin2 SIG: matches.",NONE
J3,SWD,SWD_3pad (custom),-,Pad only,"MISMATCH: symbol pin1=SWDIO, pin2=GND, pin3=SWCLK. Footprint pad1=GND, pad2=SWCLK, pad3=SWDIO.",NONE
J4,USB,USB_3pad_wire (custom),-,Pad only,"Pin1 GND, pin2 D-, pin3 D+: matches.",NONE
J5,RUN,Pad_2pad_GND_SIG (custom),-,Pad only,"Pin1 GND, pin2 SIG: matches.",NONE
J6,Servo,"NEW: 3-pad wire footprint (1 GND-switched, 2 VBAT, 3 SIG)",-,Pad only,"Order matches standard servo plug (brown, red, orange).",NONE
Q1,AO3400A,Package_TO_SOT_SMD:SOT-23,C20917,JLCPCB,,Package_TO_SOT_SMD:SOT-23
Q2,AO3400A,Package_TO_SOT_SMD:SOT-23,C20917,JLCPCB,,Package_TO_SOT_SMD:SOT-23
R1,1k,Resistor_SMD:R_0402_1005Metric,C11702,JLCPCB,,NONE
R2,22 (schematic says 27),Resistor_SMD:R_0402_1005Metric,C25092,JLCPCB,Schematic value 27 does not match bom C25092 (22 ohm). Decide one.,NONE
R3,22 (schematic says 27),Resistor_SMD:R_0402_1005Metric,C25092,JLCPCB,Schematic value 27 does not match bom C25092 (22 ohm). Decide one.,NONE
R4,1k,Resistor_SMD:R_0402_1005Metric,C11702,JLCPCB,,NONE
R5,10k,Resistor_SMD:R_0402_1005Metric,C25744,JLCPCB,,NONE
R6,10k,Resistor_SMD:R_0402_1005Metric,C25744,JLCPCB,,NONE
R7,100,Resistor_SMD:R_0402_1005Metric,C25076,JLCPCB,,NONE
R8,15R 2W axial,"(2 wire pads, no part on board)",C176558,Hand-fit (LCSC),Heater is off-board against the chamber block. Needs 2-pad footprint; exclude from bom and position files.,NONE
R9,100k,Resistor_SMD:R_0402_1005Metric,C25741,JLCPCB,,NONE
R10,100,Resistor_SMD:R_0402_1005Metric,C25076,JLCPCB,,NONE
R11,100k,Resistor_SMD:R_0402_1005Metric,C25741,JLCPCB,,NONE
R12,1k,Resistor_SMD:R_0402_1005Metric,C11702,JLCPCB,,NONE
R13,10k,Resistor_SMD:R_0402_1005Metric,C25744,JLCPCB,,NONE
R14,10k,Resistor_SMD:R_0402_1005Metric,C25744,JLCPCB,,NONE
R15,100k,Resistor_SMD:R_0402_1005Metric,C25741,JLCPCB,,NONE
R16,100k,Resistor_SMD:R_0402_1005Metric,C25741,JLCPCB,,NONE
R17,10k,Resistor_SMD:R_0402_1005Metric,C25744,JLCPCB,,NONE
R18,4.7k DNP,Resistor_SMD:R_0402_1005Metric,C25900,DNP (not ordered),"Set DNP + exclude from bom and position files, or JLCPCB bom will list them.",NONE
R19,4.7k DNP,Resistor_SMD:R_0402_1005Metric,C25900,DNP (not ordered),"Set DNP + exclude from bom and position files, or JLCPCB bom will list them.",NONE
R20,4.7k DNP,Resistor_SMD:R_0402_1005Metric,C25900,DNP (not ordered),"Set DNP + exclude from bom and position files, or JLCPCB bom will list them.",NONE
R21,4.7k DNP,Resistor_SMD:R_0402_1005Metric,C25900,DNP (not ordered),"Set DNP + exclude from bom and position files, or JLCPCB bom will list them.",NONE
SW1,SS-12D00G3,"(draw/import: 3-pin slide switch, check pitch)",C22355741,Hand-fit (LCSC),Symbol pin 2 is the common (battery side). Footprint pad 2 must be the middle pin.,NONE
TH1,NTC 10k,NEW: 2-pad wire footprint,(eBay pack of 2),Hand-wired,,NONE
TH2,NTC 10k,NEW: 2-pad wire footprint,(eBay pack of 2),Hand-wired,,NONE
TP1,3V3,TestPoint:TestPoint_Pad_D1.5mm,-,Pad only,,NONE
TP2,GND,TestPoint:TestPoint_Pad_D1.5mm,-,Pad only,,NONE
TP3,VBAT,TestPoint:TestPoint_Pad_D1.5mm,-,Pad only,,NONE
TP4,RX net (GP0),TestPoint:TestPoint_Pad_D1.5mm,-,Pad only,"GP0 is UART0 TX, so the pad named RX is the MCU transmit pin. Fine if named from the adapter side.",NONE
TP5,TX net (GP1),TestPoint:TestPoint_Pad_D1.5mm,-,Pad only,"GP0 is UART0 TX, so the pad named RX is the MCU transmit pin. Fine if named from the adapter side.",NONE
U1,RP2040,Package_DFN_QFN:QFN-56-1EP_7x7mm_P0.4mm_EP3.2x3.2mm,C2040,JLCPCB,,Package_DFN_QFN:QFN-56-1EP_7x7mm_P0.4mm_EP3.2x3.2mm
U2,W25Q128JVSIQ,Package_SO:SOIC-8_5.3x5.3mm_P1.27mm,C97521,JLCPCB,Confirm PCBA type on JLCPCB page.,Package_SO:SOIC-8_5.3x5.3mm_P1.27mm
U3,MCP1700-3302E/TO,Package_TO_SOT_THT:TO-92_Inline,C511277,Hand-fit (LCSC),Exclude from bom and position files.,Package_TO_SOT_THT:TO-92_Inline
U4,ADXL375 module,"NEW: 7-pad wire footprint (3V3,GND,SCL,SDA,SDO,CS,INT1)","(module, eBay)",Hand-wired,Currently a bare LGA-14 chip symbol with LCSC C579466. bom option 1 says C481898.,C579466:LGA-14_L5.0-W3.0-P0.80-BL-1
U5,Ra-02,RF_Module:Ai-Thinker-Ra-01-LoRa,C90039,Hand-fit (LCSC),Exclude from bom and position files. Pinout matches Ai-Thinker datasheet.,RF_Module:Ai-Thinker-Ra-01-LoRa
U6,GY-BMP280-3.3 module,"NEW: 6-pad wire footprint (3V3,GND,SCK,SDI,SDO,CSB)","(module, eBay)",Hand-wired,"Currently a bare LGA-8 chip symbol, wired as SPI. Handover said 4 pads / I2C.",Package_LGA:Bosch_LGA-8_2x2.5mm_P0.65mm_ClockwisePinNumbering
U7,TSL2591 module A,"TSL2591_module_5pad (custom) with a 1x05 symbol: 1 3V3, 2 GND, 3 SDA, 4 SCL, 5 INT","(module, AliExpress)",Hand-wired,Currently a bare TSL25911FN DFN-6 chip symbol; pin numbers do not match the custom footprint.,OptoDevice:AMS_TSL25911FN
U8,TSL2591 module B,"TSL2591_module_5pad (custom) with a 1x05 symbol: 1 3V3, 2 GND, 3 SDA, 4 SCL, 5 INT","(module, AliExpress)",Hand-wired,Currently a bare TSL25911FN DFN-6 chip symbol; pin numbers do not match the custom footprint.,OptoDevice:AMS_TSL25911FN
Y1,12MHz 20pF,Crystal:Crystal_SMD_3225-4Pin_3.2x2.5mm,C9002,JLCPCB,Value text says Crystal_GND12: rename to 12MHz.,NONE

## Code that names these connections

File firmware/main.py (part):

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PIN_UART_TX = 0       # GP0 -> /RX (TP4 UART debug, MCU TX)
PIN_UART_RX = 1       # GP1 -> /TX (TP5 UART debug, MCU RX)

PIN_INT_A = 2         # GP2 -> /INT_A (U7 TSL2591 Chamber A interrupt)
PIN_INT_B = 3         # GP3 -> /INT_B (U8 TSL2591 Chamber B interrupt)
PIN_I2C0_SDA = 4      # GP4 -> /SDA0  (U7 TSL2591 Chamber A)
PIN_I2C0_SCL = 5      # GP5 -> /SCL0  (U7 TSL2591 Chamber A)
PIN_I2C1_SDA = 6      # GP6 -> /SDA1  (U8 TSL2591 Chamber B)
PIN_I2C1_SCL = 7      # GP7 -> /SCL1  (U8 TSL2591 Chamber B)

PIN_HEATER_PWM = 8    # GP8 -> /HEATER (R7 -> Q1 AO3400A gate -> R8 15R 2W heater)
PIN_SERVO_PWR = 9     # GP9 -> /SERVO_P (R10 -> Q2 AO3400A gate -> J6 Servo GND switch)
PIN_SERVO_PWM = 10    # GP10 -> /SERVO_S (J6.3 MG90S PWM signal)

PIN_PRESS_CS = 11     # GP11 -> /PRESS_CS (U6 BMP280 CSB)
PIN_SPI1_MISO = 12    # GP12 -> /IMU_MISO (U4 ADXL375 & U6 BMP280 SDO)
PIN_IMU_CS = 13       # GP13 -> /IMU_CS   (U4 ADXL375 CS)
PIN_SPI1_SCLK = 14    # GP14 -> /IMU_SCLK (U4 ADXL375 & U6 BMP280 SCL/SCK)
PIN_SPI1_MOSI = 15    # GP15 -> /IMU_MOSI (U4 ADXL375 & U6 BMP280 SDA/SDI)

PIN_RA_MISO = 16      # GP16 -> /RA_MISO  (U5 Ra-02 SX1278 MISO)
PIN_RA_CS = 17        # GP17 -> /RA_CS    (U5 Ra-02 SX1278 NSS)
PIN_RA_SCLK = 18      # GP18 -> /RA_SCLK  (U5 Ra-02 SX1278 SCK)
PIN_RA_MOSI = 19      # GP19 -> /RA_MOSI  (U5 Ra-02 SX1278 MOSI)
PIN_RA_RESET = 20     # GP20 -> /RA_RESET (U5 Ra-02 SX1278 RESET)
PIN_RA_DIO0 = 21      # GP21 -> /RA_DIO0  (U5 Ra-02 SX1278 DIO0)

PIN_IMU_INT1 = 22     # GP22 -> /IMU_INT1 (U4 ADXL375 Shock Interrupt)
PIN_STATUS_LED = 25   # GP25 -> /LED      (R12 -> D1 Green Status LED)

PIN_BATT_SENSE = 26   # GP26 / ADC0 -> /BATT_SENSE (R15/R16 100k/100k divider)
PIN_NTC_A = 27        # GP27 / ADC1 -> /NTC_A      (TH1 Chamber A 10k NTC)
PIN_NTC_B = 28        # GP28 / ADC2 -> /NTC_B      (TH2 Chamber B 10k NTC)

# ==============================================================================
# 2. PDR Flight States (Appendix A & Appendix D)
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    servo_pwm.duty_ns(0)

    # Analog channels (ADC0=VBAT, ADC1=NTC_A, ADC2=NTC_B)
    adc_vbat = ADC(Pin(PIN_BATT_SENSE))
    adc_ntc_a = ADC(Pin(PIN_NTC_A))
    adc_ntc_b = ADC(Pin(PIN_NTC_B))

    # SPI1 for BMP280 (U6) and ADXL375 (U4)
    cs_press = Pin(PIN_PRESS_CS, Pin.OUT, value=1)
    cs_imu = Pin(PIN_IMU_CS, Pin.OUT, value=1)
    Pin(PIN_IMU_INT1, Pin.IN, Pin.PULL_DOWN)
    spi1 = SPI(
        1,
        baudrate=2_000_000,
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    # I2C0 (Chamber A TSL2591 U7) & I2C1 (Chamber B TSL2591 U8)
    i2c0 = I2C(0, scl=Pin(PIN_I2C0_SCL), sda=Pin(PIN_I2C0_SDA), freq=400_000)
    i2c1 = I2C(1, scl=Pin(PIN_I2C1_SCL), sda=Pin(PIN_I2C1_SDA), freq=400_000)
    Pin(PIN_INT_A, Pin.IN, Pin.PULL_UP)
    Pin(PIN_INT_B, Pin.IN, Pin.PULL_UP)

    lux_a = None
    lux_b = None
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        baudrate=4_000_000,
        polarity=0,
        phase=0,
        sck=Pin(PIN_RA_SCLK),
        mosi=Pin(PIN_RA_MOSI),
        miso=Pin(PIN_RA_MISO),
    )
    lora = None
    try:
        lora = SX1278(
            spi0,
            cs=Pin(PIN_RA_CS, Pin.OUT, value=1),
            rst=Pin(PIN_RA_RESET, Pin.OUT, value=1),
            dio0=Pin(PIN_RA_DIO0, Pin.IN),
            freq_mhz=433.175,
            tx_power_dbm=17,
        )
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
